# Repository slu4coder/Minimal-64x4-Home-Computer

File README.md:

# Minimal 64x4 Redux Home Computer

Here is my latest take on 1980's home computer magic: The most computer from the least logic or the shortest way from TTL to Space Invaders.

This is a free and non-commercial project. I am in no way associated with any activies selling the Minimal 64x4 as a product.
Any such activity represents a license violation. Individual licenses apply for hardware and software parts. Please refer to the
applicable documentations for detailed licensing information.

Introductory video: https://www.youtube.com/watch?v=L1oECH6rPvs

Online emulator (sorry, no Redux): https://editor.p5js.org/slu4coder/sketches/lRq1gyYR2

Reference manual: https://docs.google.com/document/d/1-nDv_8WEG1FrlO3kEK0icoYo-Z-jlhpCMiCstxGOCjQ/edit?usp=sharing

Visit my YouTube channel: https://www.youtube.com/channel/UCXYQcMpUBT3aaQKfmAVJNow

Take a look at these repositories of fellow Minimal 64x4 enthusiasts for more games and fascinating projects:

https://github.com/hans61/Minimal-64x4-Games

https://github.com/hans61/Minimal-64x4-Expansion

https://github.com/michaelkamprath/minimal-64x4-expansion-cards

https://github.com/michaelkamprath/extended-min

https://github.com/hellboy73

FEATURES

● Only 57 74HCxx logic ICs, 2x 6C1008 SRAM, 4x 39SF0x0 FLASH, NO MICROCONTROLLER!

● Textbook 'Von-Neumann' architecture, 8-bit data bus, 16-bit address bus, 24 control signals

● 64KB RAM, 512KB FLASH SSD with file system (format, load, save, dir, delete)

● Monochrome VGA output 400 x 240 pixels, PS/2, expansion port and serial UART interface

● 8MHz CPU clockrate, 1.8Mips - that's more than 4x the commonly quoted Mips value of a 6502 running at 1MHz like in a Commodore C64 or Apple II

● 256 instructions including conditional branching, subroutines, stack, word, long and zero-page operations

● 2 data registers A & B, ALU supporting ADD, SUBTRACT, AND, OR with 3 flags (negative, carry and zero)

● Full native tool-chain: MinOS, text editor, assembler, fast Python-like interpreter 'MIN'

● Cycle-exact emulator, cross-assembler (both for Windows and Linux) and classic games (TETRIS clone, Space Invaders clone, 3D Maze)

If you like this project and want to give something back, you can do so via PayPal. Thanks!

https://paypal.me/CarstenHerting
  
Have fun!

See "CHANGE LOG" for a brief summary of the recent updates.

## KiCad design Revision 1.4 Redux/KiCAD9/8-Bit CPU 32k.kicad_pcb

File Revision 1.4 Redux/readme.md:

# Revision 1.4 Redux

I have designed the Redux just for fun to make it even more minimalistic: It uses 4 ICs less than the original, which I consider quite an achievement ;-)
It is *not* fully software-compatible (although the differences are slight) to the original Minimal 64x4 since it features an improved and more orthogonal instruction set with some small microcode tweaks. The OS and API have seen improvements, too, resulting in an overall 5% performance gain and a slightly snappier feel.
The serial interface now runs on 7 data bits and the serial OUT command features hardware waiting, which was a fun thing to implement.

The folder 'KiCAD9' contains the schematics and PCB layout files.
For the bill of materials (BOM) please refer to chapter 'Hardware' of the 'Minimal 64x4 Reference Manual'. Follow the link in the root readme.md of this repo.

The folder 'Support' contains the cross-platform assembler und the emulator (Win).
The folder 'Programs' contains native Minimal 64x4 Redux code.

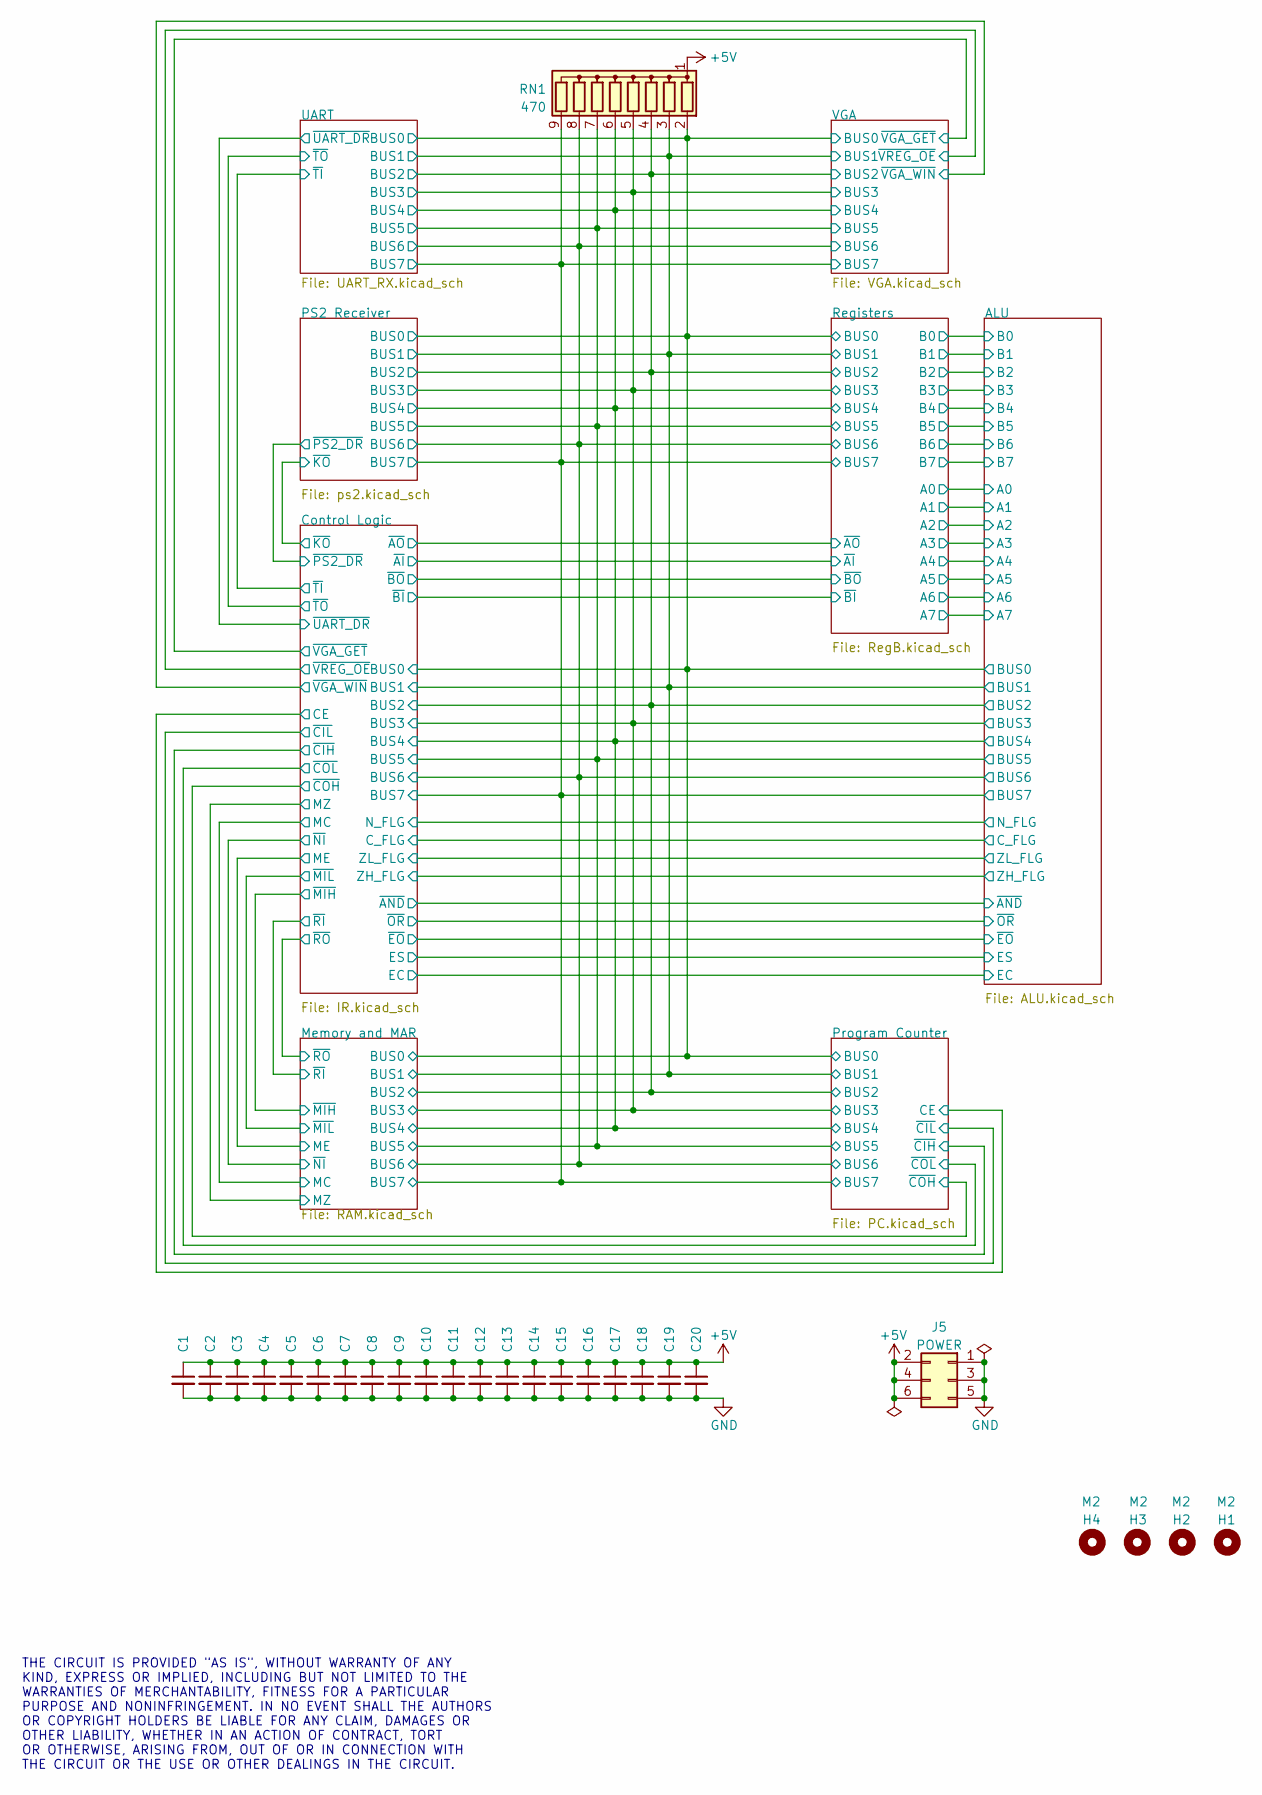
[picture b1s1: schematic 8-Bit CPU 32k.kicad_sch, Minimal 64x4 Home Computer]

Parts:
C1, C2, C3, C4, C5, C6, C7, C8, C9, C10, C11, C12, C13, C14, C15, C16, C17, C18, C19, C20: 100nF; C_Disc_D3.4mm_W2.1mm_P2.50mm
H1, H2, H3, H4: M2; MountingHole_2.2mm_M2
J5: POWER; PinSocket_2x03_P2.54mm_Vertical
RN1: 470; R_Array_SIP9

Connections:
+5V: C1.1, C2.1, C3.1, C4.1, C5.1, C6.1, C7.1, C8.1, C9.1, C10.1, C11.1, C12.1, C13.1, C14.1, C15.1, C16.1, C17.1, C18.1, C19.1, C20.1, J5.2, J5.4, J5.6, RN1.1 (common); also elsewhere on the board
/ALU/BUS0: RN1.2 (R1); also elsewhere on the board
/ALU/BUS1: RN1.3 (R2); also elsewhere on the board
/ALU/BUS2: RN1.4 (R3); also elsewhere on the board
/ALU/BUS3: RN1.5 (R4); also elsewhere on the board
/ALU/BUS4: RN1.6 (R5); also elsewhere on the board
/ALU/BUS5: RN1.7 (R6); also elsewhere on the board
/ALU/BUS6: RN1.8 (R7); also elsewhere on the board
/ALU/BUS7: RN1.9 (R8); also elsewhere on the board
GND: C1.2, C2.2, C3.2, C4.2, C5.2, C6.2, C7.2, C8.2, C9.2, C10.2, C11.2, C12.2, C13.2, C14.2, C15.2, C16.2, C17.2, C18.2, C19.2, C20.2, J5.1, J5.3, J5.5; also elsewhere on the board

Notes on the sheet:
THE CIRCUIT IS PROVIDED "AS IS", WITHOUT WARRANTY OF ANY KIND, EXPRESS OR IMPLIED, INCLUDING BUT NOT LIMITED TO THE WARRANTIES OF MERCHANTABILITY, FITNESS FOR A PARTICULAR PURPOSE AND NONINFRINGEMENT. IN NO EVENT SHALL THE AUTHORS OR COPYRIGHT HOLDERS BE LIABLE FOR ANY CLAIM, DAMAGES OR OTHER LIABI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

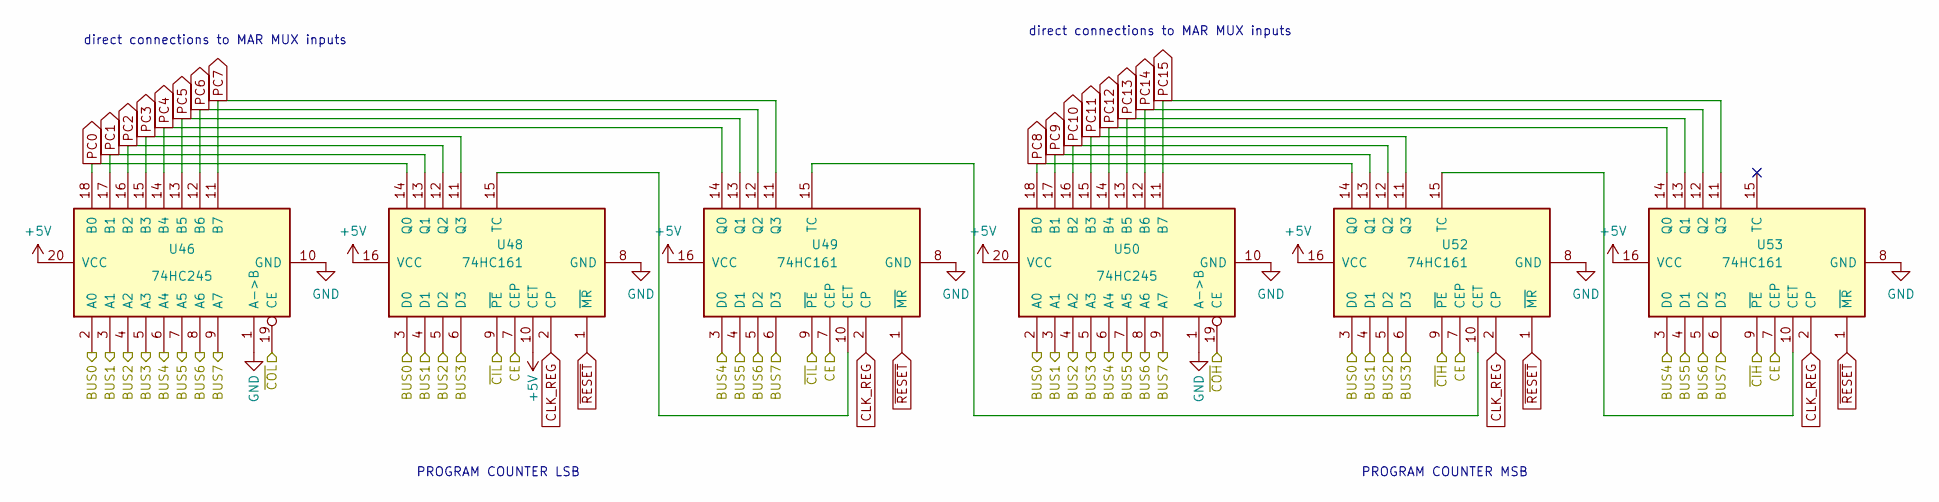
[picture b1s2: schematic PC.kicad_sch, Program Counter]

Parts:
U46, U50: 74HC245; DIP-20_W7.62mm_Socket
U48, U49, U52, U53: 74HC161; DIP-16_W7.62mm_Socket

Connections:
+5V: U46.20 (VCC), U48.10 (CET), U48.16 (VCC), U49.16 (VCC), U50.20 (VCC), U52.16 (VCC), U53.16 (VCC); also elsewhere on the board
/ALU/BUS0: U46.2 (A0), U48.3 (D0), U50.2 (A0), U52.3 (D0); also elsewhere on the board
/ALU/BUS1: U46.3 (A1), U48.4 (D1), U50.3 (A1), U52.4 (D1); also elsewhere on the board
/ALU/BUS2: U46.4 (A2), U48.5 (D2), U50.4 (A2), U52.5 (D2); also elsewhere on the board
/ALU/BUS3: U46.5 (A3), U48.6 (D3), U50.5 (A3), U52.6 (D3); also elsewhere on the board
/ALU/BUS4: U46.6 (A4), U49.3 (D0), U50.6 (A4), U53.3 (D0); also elsewhere on the board
/ALU/BUS5: U46.7 (A5), U49.4 (D1), U50.7 (A5), U53.4 (D1); also elsewhere on the board
/ALU/BUS6: U46.8 (A6), U49.5 (D2), U50.8 (A6), U53.5 (D2); also elsewhere on the board
/ALU/BUS7: U46.9 (A7), U49.6 (D3), U50.9 (A7), U53.6 (D3); also elsewhere on the board
/Control Logic/CE: U48.7 (CEP), U49.7 (CEP), U52.7 (CEP), U53.7 (CEP); also elsewhere on the board
/Control Logic/~CIH: U52.9 (~PE), U53.9 (~PE); also elsewhere on the board
/Control Logic/~CIL: U48.9 (~PE), U49.9 (~PE); also elsewhere on the board
/Control Logic/~COH: U50.19 (CE); also elsewhere on the board
/Control Logic/~COL: U46.19 (CE); also elsewhere on the board
CLK_REG: U48.2 (CP), U49.2 (CP), U52.2 (CP), U53.2 (CP); also elsewhere on the board
GND: U46.1 (A->B), U46.10 (GND), U48.8 (GND), U49.8 (GND), U50.1 (A->B), U50.10 (GND), U52.8 (GND), U53.8 (GND); also elsewhere on the board
unnamed: U48.15 (TC), U49.10 (CET)
unnamed: U49.15 (TC), U52.10 (CET)
unnamed: U52.15 (TC), U53.10 (CET)
PC0: U46.18 (B0), U48.14 (Q0); also elsewhere on the board
PC1: U46.17 (B1), U48.13 (Q1); also elsewhere on the board
PC2: U46.16 (B2), U48.12 (Q2); also elsewhere on the board
PC3: U46.15 (B3), U48.11 (Q3); also elsewhere on the board
PC4: U46.14 (B4), U49.14 (Q0); also elsewhere on the board
PC5: U46.13 (B5), U49.13 (Q1); also elsewhere on the board
PC6: U46.12 (B6), U49.12 (Q2); also elsewhere on the board
PC7: U46.11 (B7), U49.11 (Q3); also elsewhere on the board
PC8: U50.18 (B0), U52.14 (Q0); also elsewhere on the board
PC9: U50.17 (B1), U52.13 (Q1); also elsewhere on the board
PC10: U50.16 (B2), U52.12 (Q2); also elsewhere on the board
PC11: U50.15 (B3), U52.11 (Q3); also elsewhere on the board
PC12: U50.14 (B4), U53.14 (Q0); also elsewhere on the board
PC13: U50.13 (B5), U53.13 (Q1); also elsewhere on the board
PC14: U50.12 (B6), U53.12 (Q2); also elsewhere on the board
PC15: U50.11 (B7), U53.11 (Q3); also elsewhere on the board
~RESET: U48.1 (~MR), U49.1 (~MR), U52.1 (~MR), U53.1 (~MR); also elsewhere on the board

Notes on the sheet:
PROGRAM COUNTER MSB
PROGRAM COUNTER LSB
direct connections to MAR MUX inputs

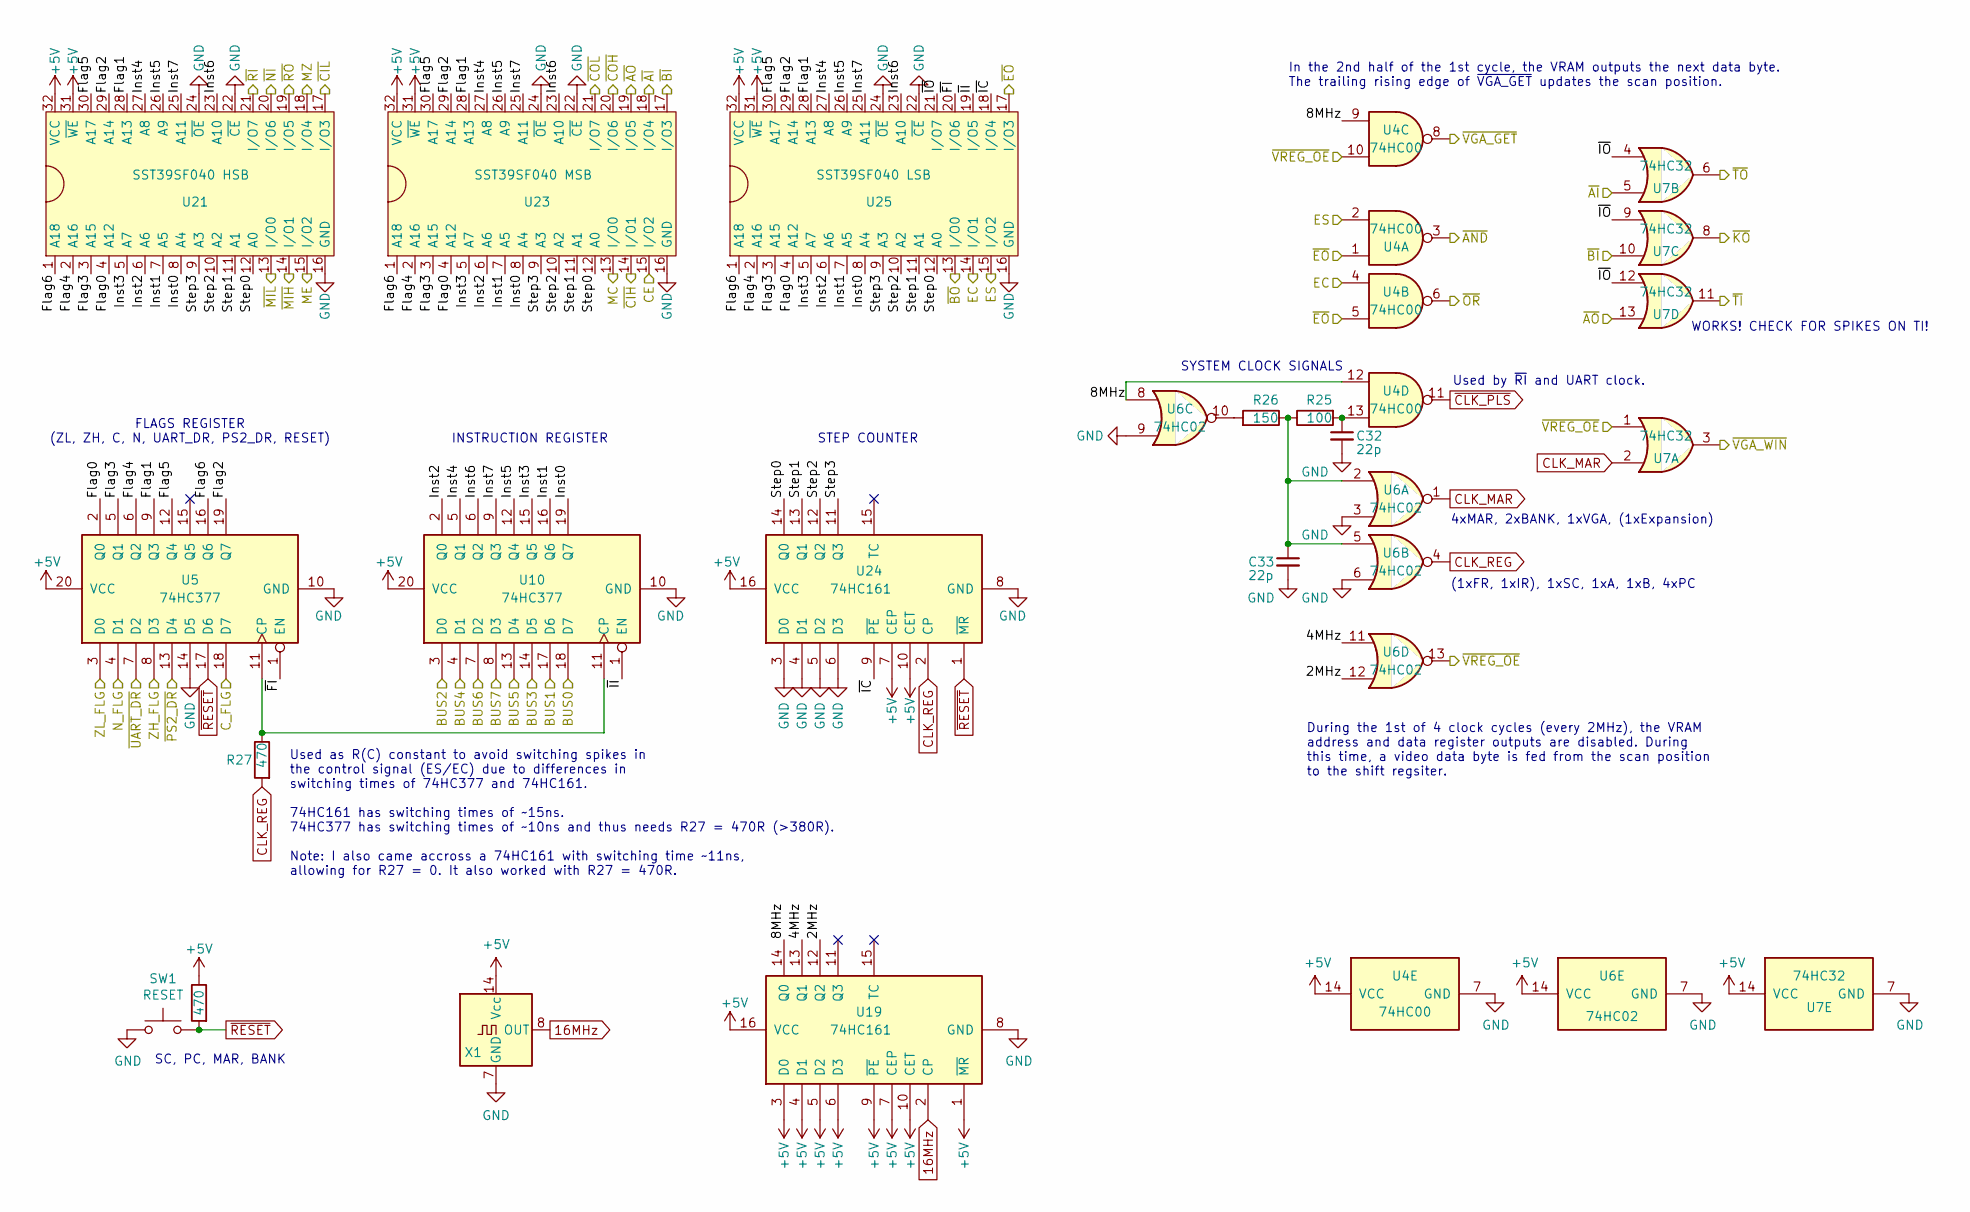
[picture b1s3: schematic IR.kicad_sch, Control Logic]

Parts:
C32, C33: 22p; C_Disc_D3.4mm_W2.1mm_P2.50mm
R2, R27: 470; R_Axial_DIN0207_L6.3mm_D2.5mm_P7.62mm_Horizontal
R25: 100; R_Axial_DIN0207_L6.3mm_D2.5mm_P7.62mm_Horizontal
R26: 150; R_Axial_DIN0207_L6.3mm_D2.5mm_P7.62mm_Horizontal
SW1: RESET; SW_PUSH_6mm
U4: 74HC00; DIP-14_W7.62mm_Socket
U5, U10: 74HC377; DIP-20_W7.62mm_Socket
U6: 74HC02; DIP-14_W7.62mm_Socket
U7: 74HC32; DIP-14_W7.62mm_Socket
U19, U24: 74HC161; DIP-16_W7.62mm_Socket
U21: SST39SF040 HSB; DIP-32_W15.24mm_Socket
U23: SST39SF040 MSB; DIP-32_W15.24mm_Socket
U25: SST39SF040 LSB; DIP-32_W15.24mm_Socket
X1: 16MHz; Oscillator_DIP-14

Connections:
16MHz: U19.2 (CP), X1.8 (OUT); also elsewhere on the board
+5V: R2.1, U4.14 (VCC), U5.20 (VCC), U6.14 (VCC), U7.14 (VCC), U10.20 (VCC), U19.1 (~MR), U19.3 (D0), U19.4 (D1), U19.5 (D2), U19.6 (D3), U19.7 (CEP), U19.9 (~PE), U19.10 (CET), U19.16 (VCC), U21.31 (~WE), U21.32 (VCC), U23.31 (~WE), U23.32 (VCC), U24.7 (CEP), U24.10 (CET), U24.16 (VCC), U25.31 (~WE), U25.32 (VCC), X1.14 (Vcc); also elsewhere on the board
/ALU/BUS0: U10.18 (D7); also elsewhere on the board
/ALU/BUS1: U10.17 (D6); also elsewhere on the board
/ALU/BUS2: U10.3 (D0); also elsewhere on the board
/ALU/BUS3: U10.14 (D5); also elsewhere on the board
/ALU/BUS4: U10.4 (D1); also elsewhere on the board
/ALU/BUS5: U10.13 (D4); also elsewhere on the board
/ALU/BUS6: U10.7 (D2); also elsewhere on the board
/ALU/BUS7: U10.8 (D3); also elsewhere on the board
/ALU/C_FLG: U5.18 (D7); also elsewhere on the board
/ALU/EC: U4.4, U25.14 (I/O1); also elsewhere on the board
/ALU/ES: U4.2, U25.15 (I/O2); also elsewhere on the board
/ALU/N_FLG: U5.4 (D1); also elsewhere on the board
/ALU/ZH_FLG: U5.8 (D3); also elsewhere on the board
/ALU/ZL_FLG: U5.3 (D0); also elsewhere on the board
/ALU/~AND: U4.3; also elsewhere on the board
/ALU/~EO: U4.1, U4.5, U25.17 (I/O3); also elsewhere on the board
/ALU/~OR: U4.6; also elsewhere on the board
/Control Logic/2MHz: U6.12, U19.12 (Q2)
/Control Logic/4MHz: U6.11, U19.13 (Q1)
/Control Logic/8MHz: U4.9, U4.12, U6.8, U19.14 (Q0)
/Control Logic/CE: U23.15 (I/O2); also elsewhere on the board
/Control Logic/Flag0: U5.2 (Q0), U21.4 (A12), U23.4 (A12), U25.4 (A12)
/Control Logic/Flag1: U5.9 (Q3), U21.28 (A13), U23.28 (A13), U25.28 (A13)
/Control Logic/Flag2: U5.19 (Q7), U21.29 (A14), U23.29 (A14), U25.29 (A14)
/Control Logic/Flag3: U5.5 (Q1), U21.3 (A15), U23.3 (A15), U25.3 (A15)
/Control Logic/Flag4: U5.6 (Q2), U21.2 (A16), U23.2 (A16), U25.2 (A16)
/Control Logic/Flag5: U5.12 (Q4), U21.30 (A17), U23.30 (A17), U25.30 (A17)
/Control Logic/Flag6: U5.16 (Q6), U21.1 (A18), U23.1 (A18), U25.1 (A18)
/Control Logic/Inst0: U10.19 (Q7), U21.8 (A4), U23.8 (A4), U25.8 (A4)
/Control Logic/Inst1: U10.16 (Q6), U21.7 (A5), U23.7 (A5), U25.7 (A5)
/Control Logic/Inst2: U10.2 (Q0), U21.6 (A6), U23.6 (A6), U25.6 (A6)
/Control Logic/Inst3: U10.15 (Q5), U21.5 (A7), U23.5 (A7), U25.5 (A7)
/Control Logic/Inst4: U10.5 (Q1), U21.27 (A8), U23.27 (A8), U25.27 (A8)
/Control Logic/Inst5: U10.12 (Q4), U21.26 (A9), U23.26 (A9), U25.26 (A9)
/Control Logic/Inst6: U10.6 (Q2), U21.23 (A10), U23.23 (A10), U25.23 (A10)
/Control Logic/Inst7: U10.9 (Q3), U21.25 (A11), U23.25 (A11), U25.25 (A11)
/Control Logic/MC: U23.13 (I/O0); also elsewhere on the board
/Control Logic/ME: U21.15 (I/O2); also elsewhere on the board
/Control Logic/MZ: U21.18 (I/O4); also elsewhere on the board
/Control Logic/Step0: U21.12 (A0), U23.12 (A0), U24.14 (Q0), U25.12 (A0)
/Control Logic/Step1: U21.11 (A1), U23.11 (A1), U24.13 (Q1), U25.11 (A1)
/Control Logic/Step2: U21.10 (A2), U23.10 (A2), U24.12 (Q2), U25.10 (A2)
/Control Logic/Step3: U21.9 (A3), U23.9 (A3), U24.11 (Q3), U25.9 (A3)
/Control Logic/~AI: U7.5, U23.18 (I/O4); also elsewhere on the board
/Control Logic/~AO: U7.13, U23.19 (I/O5); also elsewhere on the board
/Control Logic/~BI: U7.10, U23.17 (I/O3); also elsewhere on the board
/Control Logic/~BO: U25.13 (I/O0); also elsewhere on the board
/Control Logic/~CIH: U23.14 (I/O1); also elsewhere on the board
/Control Logic/~CIL: U21.17 (I/O3); also elsewhere on the board
/Control Logic/~COH: U23.20 (I/O6); also elsewhere on the board
/Control Logic/~COL: U23.21 (I/O7); also elsewhere on the board
/Control Logic/~FI: U5.1 (EN), U25.20 (I/O6)
/Control Logic/~IC: U24.9 (~PE), U25.18 (I/O4)
/Control Logic/~II: U10.1 (EN), U25.19 (I/O5)
/Control Logic/~IO: U7.4, U7.9, U7.12, U25.21 (I/O7)
/Control Logic/~KO: U7.8; also elsewhere on the board
/Control Logic/~MIH: U21.14 (I/O1); also elsewhere on the board
/Control Logic/~MIL: U21.13 (I/O0); also elsewhere on the board
/Control Logic/~NI: U21.20 (I/O6); also elsewhere on the board
/Control Logic/~PS2_DR: U5.13 (D4); also elsewhere on the board
/Control Logic/~RI: U21.21 (I/O7); also elsewhere on the board
/Control Logic/~RO: U21.19 (I/O5); also elsewhere on the board
/Control Logic/~TI: U7.11; also elsewhere on the board
/Control Logic/~TO: U7.6; also elsewhere on the board
/Control Logic/~UART_DR: U5.7 (D2); also elsewhere on the board
/Control Logic/~VGA_GET: U4.8; also elsewhere on the board
/Control Logic/~VGA_TRY: U7.3; also elsewhere on the board
/Control Logic/~VREG_OE: U4.10, U6.13, U7.1; also elsewhere on the board
CLK_MAR: U6.1, U7.2; also elsewhere on the board
CLK_REG: R27.2, U6.4, U24.2 (CP); also elsewhere on the board
GND: C32.2, C33.2, SW1.2, U4.7 (GND), U5.10 (GND), U5.14 (D5), U6.3, U6.6, U6.7 (GND), U6.9, U7.7 (GND), U10.10 (GND), U19.8 (GND), U21.16 (GND), U21.22 (~CE), U21.24 (~OE), U23.16 (GND), U23.22 (~CE), U23.24 (~OE), U24.3 (D0), U24.4 (D1), U24.5 (D2), U24.6 (D3), U24.8 (GND), U25.16 (GND), U25.22 (~CE), U25.24 (~OE), X1.7 (GND); also elsewhere on the board
unnamed: C32.1, R25.2, U4.13
unnamed: C33.1, R25.1, R26.1, U6.2, U6.5
unnamed: R26.2, U6.10
unnamed: R27.1, U5.11 (CP), U10.11 (CP)
~CLK_PLS: U4.11; also elsewhere on the board
~RESET: R2.2, SW1.1, U5.17 (D6), U24.1 (~MR); also elsewhere on the board

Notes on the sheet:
SYSTEM CLOCK SIGNALS
During the 1st of 4 clock cycles (every 2MHz), the VRAM address and data register outputs are disabled. During this time, a video data byte is fed from the scan position to the shift regsiter.
In the 2nd half of the 1st cycle, the VRAM outputs the next data byte. The trailing rising edge of ~{VGA_GET} updates the scan position.
SC, PC, MAR, BANK
Used by ~{RI} and UART clock.
INSTRUCTION REGISTER
4xMAR, 2xBANK, 1xVGA, (1xExpansion)
(1xFR, 1xIR), 1xSC, 1xA, 1xB, 4xPC
STEP COUNTER
Used as R(C) constant to avoid switching spikes in the control signal (ES/EC) due to differences in switching times of 74HC377 and 74HC161. 74HC161 has switching times of ~15ns. 74HC377 has switching times of ~10ns and thus needs R27 = 470R (>380R). Note: I also came accross a 74HC161 with switchin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
FLAGS REGISTER (ZL, ZH, C, N, UART_DR, PS2_DR, RESET)
WORKS! CHECK FOR SPIKES ON TI!

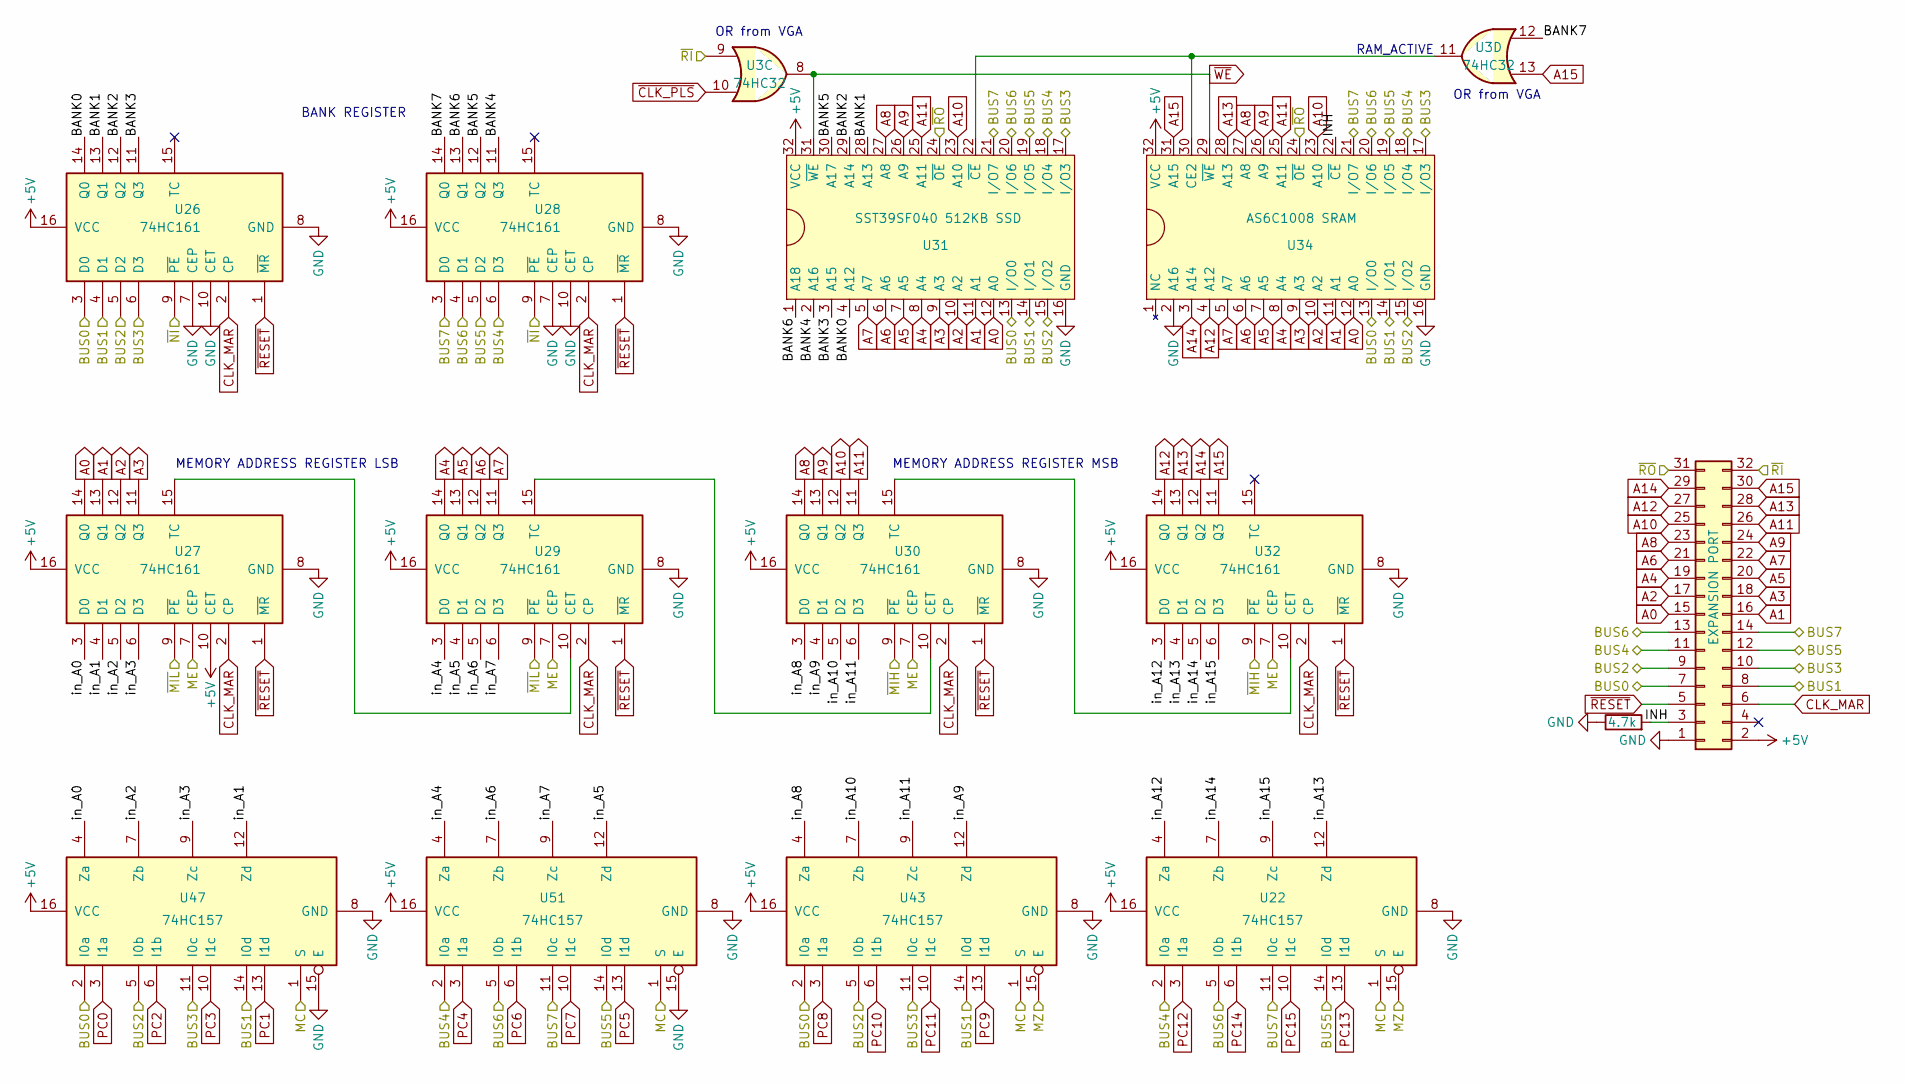
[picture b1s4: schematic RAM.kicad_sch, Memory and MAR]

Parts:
J3: EXPANSION PORT; PinSocket_2x16_P2.54mm_Vertical
R5: 4.7k; R_Axial_DIN0207_L6.3mm_D2.5mm_P7.62mm_Horizontal
U3: 74HC32; DIP-14_W7.62mm_Socket
U22, U43, U47, U51: 74HC157; DIP-16_W7.62mm_Socket
U26, U27, U28, U29, U30, U32: 74HC161; DIP-16_W7.62mm_Socket
U31: SST39SF040 512KB SSD; DIP-32_W15.24mm_Socket
U34: AS6C1008 SRAM; DIP-32_W15.24mm_Socket

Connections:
+5V: J3.2, U22.16 (VCC), U26.16 (VCC), U27.10 (CET), U27.16 (VCC), U28.16 (VCC), U29.16 (VCC), U30.16 (VCC), U31.32 (VCC), U32.16 (VCC), U34.32 (VCC), U43.16 (VCC), U47.16 (VCC), U51.16 (VCC); also elsewhere on the board
/ALU/BUS0: J3.7, U26.3 (D0), U31.13 (I/O0), U34.13 (I/O0), U43.2 (I0a), U47.2 (I0a); also elsewhere on the board
/ALU/BUS1: J3.8, U26.4 (D1), U31.14 (I/O1), U34.14 (I/O1), U43.14 (I0d), U47.14 (I0d); also elsewhere on the board
/ALU/BUS2: J3.9, U26.5 (D2), U31.15 (I/O2), U34.15 (I/O2), U43.5 (I0b), U47.5 (I0b); also elsewhere on the board
/ALU/BUS3: J3.10, U26.6 (D3), U31.17 (I/O3), U34.17 (I/O3), U43.11 (I0c), U47.11 (I0c); also elsewhere on the board
/ALU/BUS4: J3.11, U22.2 (I0a), U28.6 (D3), U31.18 (I/O4), U34.18 (I/O4), U51.2 (I0a); also elsewhere on the board
/ALU/BUS5: J3.12, U22.14 (I0d), U28.5 (D2), U31.19 (I/O5), U34.19 (I/O5), U51.14 (I0d); also elsewhere on the board
/ALU/BUS6: J3.13, U22.5 (I0b), U28.4 (D1), U31.20 (I/O6), U34.20 (I/O6), U51.5 (I0b); also elsewhere on the board
/ALU/BUS7: J3.14, U22.11 (I0c), U28.3 (D0), U31.21 (I/O7), U34.21 (I/O7), U51.11 (I0c); also elsewhere on the board
/Control Logic/MC: U22.1 (S), U43.1 (S), U47.1 (S), U51.1 (S); also elsewhere on the board
/Control Logic/ME: U27.7 (CEP), U29.7 (CEP), U30.7 (CEP), U32.7 (CEP); also elsewhere on the board
/Control Logic/MZ: U22.15 (E), U43.15 (E); also elsewhere on the board
/Control Logic/~MIH: U30.9 (~PE), U32.9 (~PE); also elsewhere on the board
/Control Logic/~MIL: U27.9 (~PE), U29.9 (~PE); also elsewhere on the board
/Control Logic/~NI: U26.9 (~PE), U28.9 (~PE); also elsewhere on the board
/Control Logic/~RI: J3.32, U3.9; also elsewhere on the board
/Control Logic/~RO: J3.31, U31.24 (~OE), U34.24 (~OE); also elsewhere on the board
/Memory and MAR/BANK0: U26.14 (Q0), U31.4 (A12)
/Memory and MAR/BANK1: U26.13 (Q1), U31.28 (A13)
/Memory and MAR/BANK2: U26.12 (Q2), U31.29 (A14)
/Memory and MAR/BANK3: U26.11 (Q3), U31.3 (A15)
/Memory and MAR/BANK4: U28.11 (Q3), U31.2 (A16)
/Memory and MAR/BANK5: U28.12 (Q2), U31.30 (A17)
/Memory and MAR/BANK6: U28.13 (Q1), U31.1 (A18)
/Memory and MAR/BANK7: U3.12, U28.14 (Q0)
/Memory and MAR/INH: J3.3, R5.2, U34.22 (~CE)
/Memory and MAR/in_A0: U27.3 (D0), U47.4 (Za)
/Memory and MAR/in_A1: U27.4 (D1), U47.12 (Zd)
/Memory and MAR/in_A2: U27.5 (D2), U47.7 (Zb)
/Memory and MAR/in_A3: U27.6 (D3), U47.9 (Zc)
/Memory and MAR/in_A4: U29.3 (D0), U51.4 (Za)
/Memory and MAR/in_A5: U29.4 (D1), U51.12 (Zd)
/Memory and MAR/in_A6: U29.5 (D2), U51.7 (Zb)
/Memory and MAR/in_A7: U29.6 (D3), U51.9 (Zc)
/Memory and MAR/in_A8: U30.3 (D0), U43.4 (Za)
/Memory and MAR/in_A9: U30.4 (D1), U43.12 (Zd)
/Memory and MAR/in_A10: U30.5 (D2), U43.7 (Zb)
/Memory and MAR/in_A11: U30.6 (D3), U43.9 (Zc)
/Memory and MAR/in_A12: U22.4 (Za), U32.3 (D0)
/Memory and MAR/in_A13: U22.12 (Zd), U32.4 (D1)
/Memory and MAR/in_A14: U22.7 (Zb), U32.5 (D2)
/Memory and MAR/in_A15: U22.9 (Zc), U32.6 (D3)
A0: J3.15, U27.14 (Q0), U31.12 (A0), U34.12 (A0); also elsewhere on the board
A1: J3.16, U27.13 (Q1), U31.11 (A1), U34.11 (A1); also elsewhere on the board
A2: J3.17, U27.12 (Q2), U31.10 (A2), U34.10 (A2); also elsewhere on the board
A3: J3.18, U27.11 (Q3), U31.9 (A3), U34.9 (A3); also elsewhere on the board
A4: J3.19, U29.14 (Q0), U31.8 (A4), U34.8 (A4); also elsewhere on the board
A5: J3.20, U29.13 (Q1), U31.7 (A5), U34.7 (A5); also elsewhere on the board
A6: J3.21, U29.12 (Q2), U31.6 (A6), U34.6 (A6); also elsewhere on the board
A7: J3.22, U29.11 (Q3), U31.5 (A7), U34.5 (A7); also elsewhere on the board
A8: J3.23, U30.14 (Q0), U31.27 (A8), U34.27 (A8); also elsewhere on the board
A9: J3.24, U30.13 (Q1), U31.26 (A9), U34.26 (A9); also elsewhere on the board
A10: J3.25, U30.12 (Q2), U31.23 (A10), U34.23 (A10); also elsewhere on the board
A11: J3.26, U30.11 (Q3), U31.25 (A11), U34.25 (A11); also elsewhere on the board
A12: J3.27, U32.14 (Q0), U34.4 (A12); also elsewhere on the board
A13: J3.28, U32.13 (Q1), U34.28 (A13); also elsewhere on the board
A14: J3.29, U32.12 (Q2), U34.3 (A14); also elsewhere on the board
A15: J3.30, U3.13, U32.11 (Q3), U34.31 (A15); also elsewhere on the board
CLK_MAR: J3.6, U26.2 (CP), U27.2 (CP), U28.2 (CP), U29.2 (CP), U30.2 (CP), U32.2 (CP); also elsewhere on the board
GND: J3.1, R5.1, U22.8 (GND), U26.7 (CEP), U26.8 (GND), U26.10 (CET), U27.8 (GND), U28.7 (CEP), U28.8 (GND), U28.10 (CET), U29.8 (GND), U30.8 (GND), U31.16 (GND), U32.8 (GND), U34.2 (A16), U34.16 (GND), U43.8 (GND), U47.8 (GND), U47.15 (E), U51.8 (GND), U51.15 (E); also elsewhere on the board
unnamed: U27.15 (TC), U29.10 (CET)
unnamed: U29.15 (TC), U30.10 (CET)
unnamed: U30.15 (TC), U32.10 (CET)
unnamed: U3.11, U31.22 (~CE), U34.30 (CE2)
PC0: U47.3 (I1a); also elsewhere on the board
PC1: U47.13 (I1d); also elsewhere on the board
PC2: U47.6 (I1b); also elsewhere on the board
PC3: U47.10 (I1c); also elsewhere on the board
PC4: U51.3 (I1a); also elsewhere on the board
PC5: U51.13 (I1d); also elsewhere on the board
PC6: U51.6 (I1b); also elsewhere on the board
PC7: U51.10 (I1c); also elsewhere on the board
PC8: U43.3 (I1a); also elsewhere on the board
PC9: U43.13 (I1d); also elsewhere on the board
PC10: U43.6 (I1b); also elsewhere on the board
PC11: U43.10 (I1c); also elsewhere on the board
PC12: U22.3 (I1a); also elsewhere on the board
PC13: U22.13 (I1d); also elsewhere on the board
PC14: U22.6 (I1b); also elsewhere on the board
PC15: U22.10 (I1c); also elsewhere on the board
~CLK_PLS: U3.10; also elsewhere on the board
~RESET: J3.5, U26.1 (~MR), U27.1 (~MR), U28.1 (~MR), U29.1 (~MR), U30.1 (~MR), U32.1 (~MR); also elsewhere on the board
~WE: U3.8, U31.31 (~WE), U34.29 (~WE); also elsewhere on the board

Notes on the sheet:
MEMORY ADDRESS REGISTER MSB
OR from VGA
MEMORY ADDRESS REGISTER LSB
RAM_ACTIVE
BANK REGISTER

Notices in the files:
Revision 1.1/KiCAD/8-Bit CPU 32k.kicad_sch:
creativecommons.org/licenses/by-nc-sa/4.0
This work is licensed under CC BY-NC-SA 4.0
Revision 1.1/KiCAD8/8-Bit CPU 32k.kicad_pcb:
Licensed under CC BY-NC-SA 4.0  http://creativecommons.org/licenses/by-nc-sa/4.0
